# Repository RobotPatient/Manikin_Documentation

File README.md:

# Manikin_Documentation

The purpose of this repository is to have one place for all relevant contributions to the Manikin project.

This repo contains the Documentation for the SensorHubs and mainboard of the manikin (BLS - Basic Life Support).

In the _archive folder, you can find the previous work of the subprojects contribution.

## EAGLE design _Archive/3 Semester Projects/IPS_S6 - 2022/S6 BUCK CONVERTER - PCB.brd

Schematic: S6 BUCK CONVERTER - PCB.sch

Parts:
C1: 100uF; CAPAE830X1050N
C3, C4, C18, C19: 10uF; CAPC1608X85
C5, C17: 33uF; CAPPRD550W60D1200H2000B
C8: 15nF; CAPC1608X85
C9, C13: 33nF; CAPC1608X85
C10, C11: 10uF; CAPC3216X135
C12: 4.7uF; CAPC1608X85
C14, C16: 470pF; CAPC1608X85
C15: 10nF; CAPC1608X85
D1, D2: MBRA140; SMA-DIODE
J1, J2, J3: CONN_02; 1X02
L1, L2: INDUCTOR-18UH
Q1: 310mA/60V/1.6Ω; SOT323
R1, R3: 51 ohm; 0603-RES
R2: 20K ohm; 0603-RES
R4: 3.83k ohm; 0603-RES
R5: 277 ohm; 0603-RES
R6, R10: 10 ohm; 0603-RES
R7: 6.34k ohm; 0603-RES
R8: 470 ohm; 0603-RES
R9: 20k ohm; 0603-RES
TP1, TP2, TP3, TP4, TP5, TP6, TP7, TP8, TP9, TP10, TP12, TP13, TP14, TP15, TP16, TP17, TP18, TP19: TEST-POINT3X5; PAD.03X.05
U$1: TPS54286; PWP14_2P31X2P46-L

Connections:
3.3V: C17.1 (+), C18.2, C19.2, J3.1, L2.2, R3.2, TP16.P$1, TP18.P$1
5V: C3.2, C4.2, C5.1 (+), J2.1, L1.2, R1.1, TP3.P$1, TP6.P$1
GND: C1.2 (-), C3.1, C4.1, C5.2 (-), C10.2, C11.2, C12.1, C17.2 (-), C18.1, C19.1, D1.A, D2.A, J1.2, J2.2, J3.2, Q1.2 (S), R4.2, R5.2, R6.2, R7.2, R8.2, R10.2, TP2.P$1, TP4.P$1, TP5.P$1, TP7.P$1, TP10.P$1, TP13.P$1, TP15.P$1, TP17.P$1, TP19.P$1, U$1.*EN2, U$1.EPAD, U$1.GND
unnamed: C9.2, U$1.BOOT1
unnamed: C13.1, U$1.BOOT2
unnamed: C14.1, R6.1
unnamed: C13.2, C16.2, D2.C, L2.1, TP12.P$1, U$1.SW2
unnamed: C16.1, R10.1
unnamed: C9.1, C14.2, D1.C, L1.1, TP9.P$1, U$1.SW1
unnamed: C12.2, U$1.BP
unnamed: C8.2, R2.2, R4.1, U$1.FB1
unnamed: C8.1, R5.1
unnamed: C15.1, R7.1
unnamed: C1.1 (+), C10.1, C11.1, J1.1, Q1.3 (D), TP1.P$1, U$1.*EN1, U$1.PVDD1, U$1.PVDD2
unnamed: C15.2, R8.1, R9.1, U$1.FB2
unnamed: R3.1, R9.2, TP14.P$1
unnamed: R1.2, R2.1, TP8.P$1

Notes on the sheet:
Vin 9.6 -13.2V
MCU Signal
Vout(1) 5V
Vout(2) 3.3V

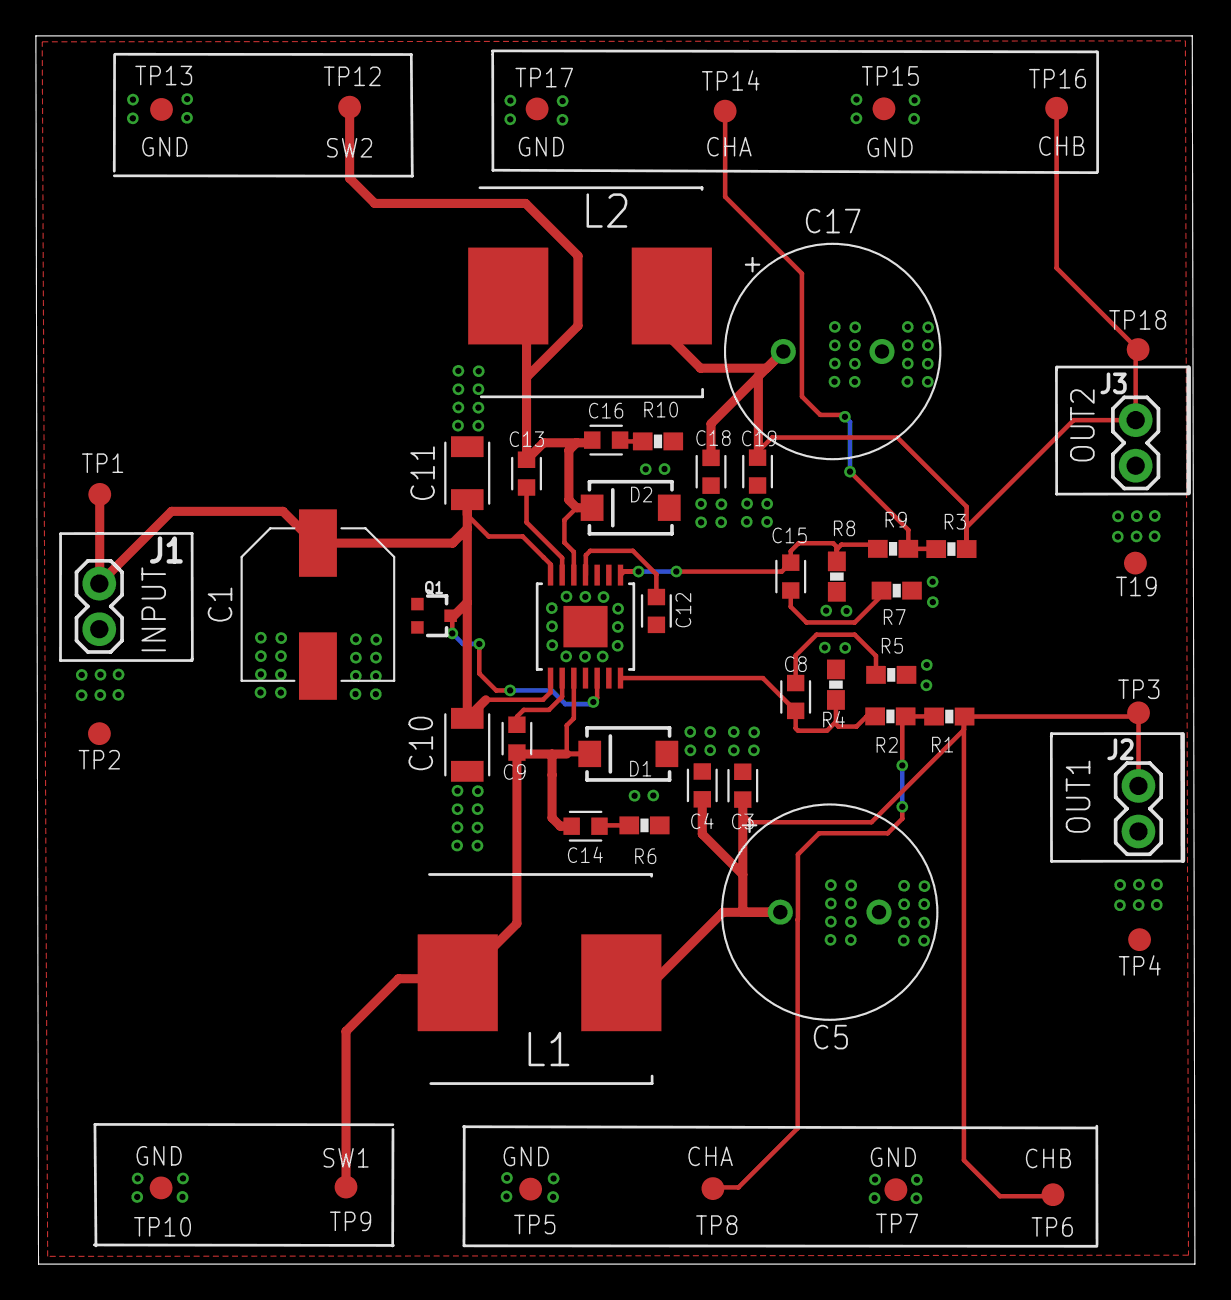
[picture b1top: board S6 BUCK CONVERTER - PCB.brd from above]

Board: 2 copper layers, 64.6 x 68.4 mm, 53 parts (0 on the bottom side), 17 nets.

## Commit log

2023-02-14 -add previous files -rm duplicates and corrupt files -enh reorganized in folders structure
    -todo: revision of _archive for relevance and overview to make it searchable in the future.
2023-02-14 -enh: added Git Large Files Storage to upload large files over 50MB: videos and powerpoints.
2023-02-14 -enh: large git files fix.
2023-02-14 Annother attempt to fix large files commit.

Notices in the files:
parts and their libraries:
SparkFun-DiscreteSemi: Licensing: Creative Commons ShareAlike 4.0 International - https://creativecommons.org/licenses/by-sa/4.0
SparkFun: Licensing: CC v3.0 Share-Alike You are welcome to use this library for commercial purposes.
